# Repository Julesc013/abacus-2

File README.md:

# Project Codename: Abacus 2

**Carbon A1 Minicomputer** and **Carbon Z1 Microcomputer**

[Project Abacus 2 Technical Reference](https://github.com/Julesc013/abacus-2/blob/main/info/manual/Abacus%202%20Technical%20Reference.pdf) (PDF)

## Specifications

- _CPU:_ **Abacus 2** or **Zilog Z80** (8-bit CISC)
- _FPU:_ **AMD Am9511** (Pre-IEEE 754)
- _Clock:_ Up to **16 MHz** (Crystal FM)
- _RAM:_ Up to **640 KB** (SRAM)
- _ROM:_ Up to **128 KB** (PROM)
- _I/O:_ Up to **256 KB** (Memory Mapped)
- _TDD:_ **Compact Cassette** (KCS 240KB/hr)
- _FDD:_ **Floppy Disk** (5.25" DSDD 360KB, 3.5" DSHD 1.44MB)
- _Comms:_ **Serial** (RS-232), **Parallel** (DB-25)
- _Video:_ **Yamaha V9958** or **TMS9918**
- _Audio:_ **Yamaha OPNB** or **AY-3-8910**

## Design Showcase

### System Architecture

16-bit CISC (Von Neumann)

### Memory and I/O

Up to 640KB SRAM (8-bit bytes)

Up to 128KB PROM (8-bit bytes)

Up to 256KB memory mapped I/O.

### Instruction Set

Abacus ISA (44 instructions) or Z80 ISA.

Integrated FPU (AMD AM9511)

### Interrupt Handling

16 hardware int's, 110 software int's, 1 non-maskable int, 1 reset int; or Z80 Mode 2 interrupt scheme.

### Video Output

VESA compatible (maybe)

### System Firmware

Resident monitor, loaders, system routines, etc.

## Physical Case

## User Manual

[Abacus 2 Technical Reference](https://github.com/Julesc013/abacus-2/blob/main/info/manual/Abacus%202%20Technical%20Reference.pdf) (PDF)

## Directory Structure
```
├── archive             Archived and old versions of files.
├── hardware            Hardware design and circuitry.
│   ├── case                Physical design of machine.
│   ├── cassette            Cassette tape data storage.
│   ├── chipset             Northbridge, southbridge, I/O, wait states, etc.
│   ├── floppy              Floppy diskette data storage.
│   ├── instructions        Instruction set architecture.
│   ├── interrupts          Interrupt tables and circuits.
│   ├── memory              Memory maps, wait states, DMA, etc.
│   ├── printer             Parallel ports and printer communication.
│   ├── serial              Serial ports and teletype communication.
│   ├── todo                Todo lists and general notes.
│   └── video               Video text and graphics output.
├── info                General project information and metadata.
│   ├── datasheets          Relevant datasheets.
│   ├── manual              User and technical manuals for the system.
│   └── parts               Parts lists and records.
├── schematics          Schematics and technical drawings.
├── simulation          Virtual simulation of processor.
│   ├── digital             Implementation in Digital.
│   └── logisim             Implementation in Logisim Evolution.   
└── software            Software, firmware, drivers, operating systems, etc.
    ├── assembler           Assembler and linker.
    ├── basic               Implementation of Microsoft 8K BASIC.
    ├── bios                Disk loaders, bootstrappers, system calls, etc.
    ├── compiler            Compiler for K&R C.
    └── executables         Executable file formats and disk formats.
```

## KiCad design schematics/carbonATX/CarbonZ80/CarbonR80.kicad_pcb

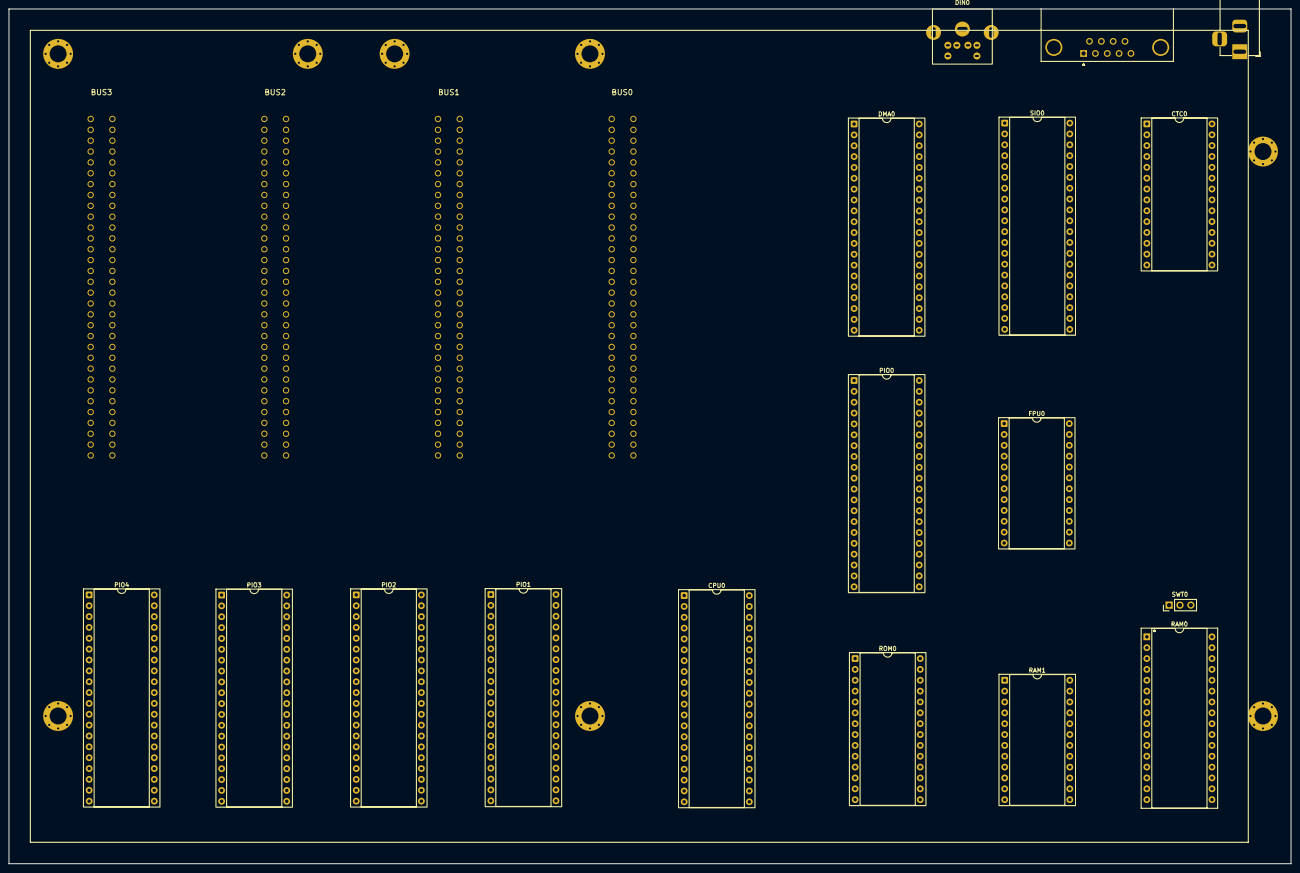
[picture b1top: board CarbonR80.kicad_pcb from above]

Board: 2 copper layers, 300.0 x 200.0 mm, 21 parts (0 on the bottom side), 26 nets, no tracks yet.

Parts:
BUS0: BUS_SLOT1; 8bISA_64pin
BUS1: BUS_SLOT2; 8bISA_64pin
BUS2: BUS_SLOT3; 8bISA_64pin
BUS3: BUS_SLOT4; 8bISA_64pin
COM0: DE9_SOCKET; DSUB-9_Socket_Horizontal_P2.77x2.84mm_EdgePinOffset7.70mm_H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
CPU0: Z84C00; DIP-40_W15.24mm_Socket
CTC0: Z84C30; DIP-28_W15.24mm_Socket
DIN0: MINI_DIN_KEYB; Mini_DIN_6
DMA0: Z84C10; DIP-40_W15.24mm_Socket
FPU0: AM9511A; DIP-24_W15.24mm_Socket
PIO0, PIO1, PIO2, PIO3, PIO4: Z84C20; DIP-40_W15.24mm_Socket
PWR0: BARREL_JACK_5.5x2.1; BarrelJack_Horizontal
RAM0: AS6C4008; DIP-32_W15.24mm_Socket
RAM1: IDT6116; DIP-24_W15.24mm_Socket
ROM0: AT28C64B; DIP-28_W15.24mm_Socket
SIO0: Z84C42; DIP-40_W15.24mm_Socket
SWT0: RAM_SIZE_SEL; PinHeader_1x03_P2.54mm_Vertical

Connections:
GND: CPU0.29 (GND), CTC0.5 (GND), DMA0.30 (GND), DMA0.38 (IEI), FPU0.1 (VSS), PIO0.11 (GND), PIO1.11 (GND), PIO2.11 (GND), PIO2.22 (IEO), PIO3.11 (GND), PIO3.24 (IEI), PIO4.11 (GND), RAM0.16 (VSS), RAM1.12 (GND), ROM0.14 (GND), SIO0.7 (IEO), SIO0.31 (GND)
unnamed: CPU0.16 (~INT), CTC0.12 (~INT), DMA0.37 (~INT/PULSE), PIO0.23 (~INT), PIO1.23 (~INT), PIO2.23 (~INT), PIO3.23 (~INT), PIO4.23 (~INT), SIO0.5 (~INT)
unnamed: CPU0.20 (~IORQ), CTC0.10 (~IORQ), DMA0.10 (~IORQ)
unnamed: CPU0.19 (~MREQ), DMA0.12 (~MREQ)
unnamed: CPU0.21 (~RD), CTC0.6 (~RD), DMA0.9 (~RD), RAM0.24 (OE#), RAM1.20 (~OE), ROM0.22 (~OE/Vpp)
unnamed: CPU0.24 (~WAIT), CTC0.14 (~M1), DMA0.26 (~M1)
unnamed: CPU0.22 (~WR), DMA0.8 (~WR), RAM0.29 (WE#), RAM1.21 (~WE)
unnamed: CTC0.11 (IEO), SIO0.6 (IEI)
unnamed: CTC0.8 (ZC/TO1), SIO0.27 (~TXCB), SIO0.28 (~RXCB)
unnamed: CTC0.9 (ZC/TO2), SIO0.13 (~RXCA), SIO0.14 (~TXCA)
unnamed: DMA0.36 (IEO), PIO0.24 (IEI)
unnamed: DMA0.25 (RDY), SIO0.30 (~W/~RDYB)
unnamed: FPU0.8 (DB0), PIO0.15 (PA0)
unnamed: FPU0.9 (DB1), PIO0.14 (PA1)
unnamed: FPU0.10 (DB2), PIO0.13 (PA2)
unnamed: FPU0.11 (DB3), PIO0.12 (PA3)
unnamed: FPU0.12 (DB4), PIO0.10 (PA4)
unnamed: FPU0.13 (DB5), PIO0.9 (PA5)
unnamed: FPU0.14 (DB6), PIO0.8 (PA6)
unnamed: FPU0.15 (DB7), PIO0.7 (PA7)
unnamed: PIO0.22 (IEO), PIO1.24 (IEI)
unnamed: PIO1.22 (IEO), PIO2.24 (IEI)
unnamed: PIO3.22 (IEO), PIO4.24 (IEI)
unnamed: RAM0.22 (CE#), SWT0.3
unnamed: RAM1.18 (~CS), SWT0.1
VCC: CPU0.11 (VCC), CTC0.13 (IEI), CTC0.24 (+5V), DMA0.11 (VCC), FPU0.2 (VCC), PIO0.26 (VCC), PIO1.26 (VCC), PIO2.26 (VCC), PIO3.26 (VCC), PIO4.26 (VCC), RAM0.32 (VCC), RAM1.24 (VCC), ROM0.28 (VCC), SIO0.9 (+5V)

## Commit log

2024-10-08 upload files
2024-10-08 moved files around
2024-10-15 Create temp
2024-10-17 Add files via upload
    changed some details from abacus 1 to abacus2/carbon1
2024-10-31 UPDATED VIDEO RESOLUTIONS
2025-01-28 Add files via upload
    Version 5V, supercedes v5.1. See also 5V Lite and 5V Core.
2025-01-28 Version 5V, Lite, and Core.
    fixed spelling errors
2025-01-28 UPDATE: Version 5V, 5V Lite, and 5V Core.
2025-01-29 Add files via upload
    formatting
2025-01-29 Add files via upload
    adjusted banked regions
2025-02-22 created KiCad project for Carbon Z80
2025-02-22 Script to generate mobo pcbs
    generates standardized layouts and slots
2025-02-22 created 200x300 pcb layout
2025-02-23 added 4 slot version
2025-02-26 placed objects yo
2025-02-26 fixed rough layout
2025-02-26 updated memory map
    took into account the fact that execution starts at 0x0000.
2025-02-26 more updates
2025-03-06 more progress
2025-03-11 pdfs
2025-03-11 fixed edge cuts
2025-03-11 big updates
2025-03-11 fixes on sch, pdf old
2025-07-16 started new rc2014 design
2025-07-16 small chg
